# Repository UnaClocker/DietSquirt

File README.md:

# DietSquirt
Version 4.0 PCB Update October 2026
Migrated to KiCad 10.0, no more legacy Eagle requirements. The board is a 4 layer 100x100mm PCB now. Updated some components, 
switched to more common and standard sized components. As of the time of this writing, the boards are in production.
Included injector and coil drivers both this time. I know the injector drivers I picked will work with at least 2x 
high impedance injectors each.
I will update as needed with the results of the first test batch. Included the exact gerbers I submitted, but I have
made some minor changes to the silkscreen on the back of the PCB since then. One way or another, I'd like to have a 
functioning PCB to use in a vehicle in the next month, so this version will be fully tested here soon.
B&G actually sent me a cease and desist back when I first released this 10 years ago. Based on some obscure patent.
Well, it's been long enough that a patent would have expired by now. Given they started MegaSquirt around 2002, 
patents only last 17 years and it's going on 25 now... I kept the Anonymous name on there to keep up the rebel
spirit of this thing.
I still have a pile of MS1 CPU's, so this board is still 68hc908 centric. But a minor refactoring would make it 
perfectly happy with the MS2 CPU module or even MS3.

--- Old notes circa 2017 ---

Low cost DIY open source MegaSquirt derivative.

Welcome to my incomplete project. This was meant to be a much cheaper 
alternative to MegaSquirt. It uses the same processor as the MegaSquirt,
which is wired the same way as you might wire it for MegaSquirt-Extra 
firmware. Now being that this is not a licensed board, you shouldn’t run 
their firmware on it. But if you do, who am I to stop you. ;) You’re not 
supposed to run MegaSquirt on street cars either, but most MegaSquirt users 
do.

Please watch the video about this: https://www.youtube.com/watch?v=LJTZ3sH1d-M

This project is licensed under the BSD License. Take it and do anything with
it. If you mass produce and sell it, I hope you’re not using the MegaSquirt 
firmware, their lawyers will bury you. Your own personal use, totally another 
matter, not worth coming after Joe Blow who’s running it in their own car. 
Ideally, the MegaSquirt firmware can prove the board, then we can switch to 
a far better processor and far more open firmware like the STM32F4 with 
RusEFI firmware. I signed the board “Anonymous” because of the risk of 
B&G’s lawyers. 

As stated, this board is a work in progress. I’d like to say I can come 
back and finish it, but I designed it two years ago, maybe 2 1/2 years at 
this point. Right after that I discovered my wife was having an affair 
(TMI…), and entered a long drawn out divorce. Now I’m a single father of 
two kids so I don’t have much time to devote to these projects anymore. 
I’m placing the files on Github, we can work together to update and fix 
the board as testing progresses.
Current known issues: 
	The components for the voltage regulator circuit are too big and 
don’t fit. Namely the capacitors. 
	It needs the LC filter added between the output of the VR and the 
rest of the board to clean up the noise from the switch mode power supply. 
See the data sheet to the 34063 voltage regulator for that circuit.
	The DB15 and DB25 connectors are too far inboard, they need to be 
shifted out to the next mark on the silkscreen.

Next up, this board does not have onboard injector drivers. I had intended 
it to use the JBPerf P&H board. He seems to have stopped selling it since 
then, so I, or someone else may need to create a clone of his old board. 
It’s a very very simple circuit board to make. The chips are still available.

You can submit the .brd files to OSHPark.com to have 3 copies of the board 
made. It’s VERY expensive there. but if you’re in the US, they’re very fast. 
You can get 10 boards made at www.elecrow.com, under their 5cmx10cm pricing, 
I believe it’s $20 for 10 boards. Give the spare boards to friends, or save 
them as spares. Don’t sell them, you’ll risk the wrath of the B&G lawyers.

See the attached BOM for the list of parts you’ll want to order from Digikey 
for this board.

The files are for Eagle. Place the .brd and .sch files in a DietSquirt folder
under your main eagle projects, then load the .sch schematic file and .brd board 
layout file. The gerbers are included, but since the board needs work still, 
I wouldn't suggest building having it produced. At the very least, you'd have 
to run an external 5v voltage regulator. I'd have prefered to have done the 
board in KiCad, but I knew Eagle better at the time. You can get a free version 
of Eagle, google it, download it. Works in all 3 major OS's.

I’m probably forgetting a lot. I’ll document more as time allows. 
Questions? unaclocker@gmail.com

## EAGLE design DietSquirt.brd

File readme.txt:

Welcome to my incomplete project. This was meant to be a much cheaper 
alternative to MegaSquirt. It uses the same processor as the MegaSquirt,
which is wired the same way as you might wire it for MegaSquirt-Extra 
firmware. Now being that this is not a licensed board, you shouldn’t run 
their firmware on it. But if you do, who am I to stop you. ;) You’re not 
supposed to run MegaSquirt on street cars either, but most MegaSquirt users 
do.
Please watch the video about this which will be posted on YouTube shortly.
This project is licensed under the BSD License. Take it and do anything with
it. If you mass produce and sell it, I hope you’re not using the MegaSquirt 
firmware, their lawyers will bury you. Your own personal use, totally another 
matter, not worth coming after Joe Blow who’s running it in their own car. 
Ideally, the MegaSquirt firmware can prove the board, then we can switch to 
a far better processor and far more open firmware like the STM32F4 with 
RusEFI firmware. I signed the board “Anonymous” because of the risk of 
B&G’s lawyers. 
As stated, this board is a work in progress. I’d like to say I can come 
back and finish it, but I designed it two years ago, maybe 2 1/2 years at 
this point. Right after that I discovered my wife was having an affair 
(TMI…), and entered a long drawn out divorce. Now I’m a single father of 
two kids so I don’t have much time to devote to these projects anymore. 
I’m placing the files on Github, we can work together to update and fix 
the board as testing progresses.
Current known issues: 
	The components for the voltage regulator circuit are too big and 
don’t fit. Namely the capacitors. 
	It needs the LC filter added between the output of the VR and the 
rest of the board to clean up the noise from the switch mode power supply. 
See the data sheet to the 34063 voltage regulator for that circuit.
	The DB15 and DB25 connectors are too far inboard, they need to be 
shifted out to the next mark on the silkscreen.

Next up, this board does not have onboard injector drivers. I had intended 
it to use the JBPerf P&H board. He seems to have stopped selling it since 
then, so I, or someone else may need to create a clone of his old board. 
It’s a very very simple circuit board to make. The chips are still available.

You can submit the .brd files to OSHPark.com to have 3 copies of the board 
made. It’s VERY expensive there. but if you’re in the US, they’re very fast. 
You can get 10 boards made at www.elecrow.com, under their 5cmx10cm pricing, 
I believe it’s $20 for 10 boards. Give the spare boards to friends, or save 
them as spares. Don’t sell them, you’ll risk the wrath of the B&G lawyers.

See the attached BOM for the list of parts you’ll want to order from Digikey 
for this board.

The files are for Eagle. Load the .pro project file, then load the .sch 
schematic file and .brd board layout file. The gerbers are included, but 
since the board needs work still, I wouldn't suggest building it. At the 
very least, you'd have to run an external 5v voltage regulator. I'd have 
prefered to have done the board in KiCad,
but I knew Eagle better at the time. You can get a free version of Eagle, 
google it, download it. Works in all 3 major OS's.

I’m probably forgetting a lot. I’ll document more as time allows. 
Questions? unaclocker@gmail.com

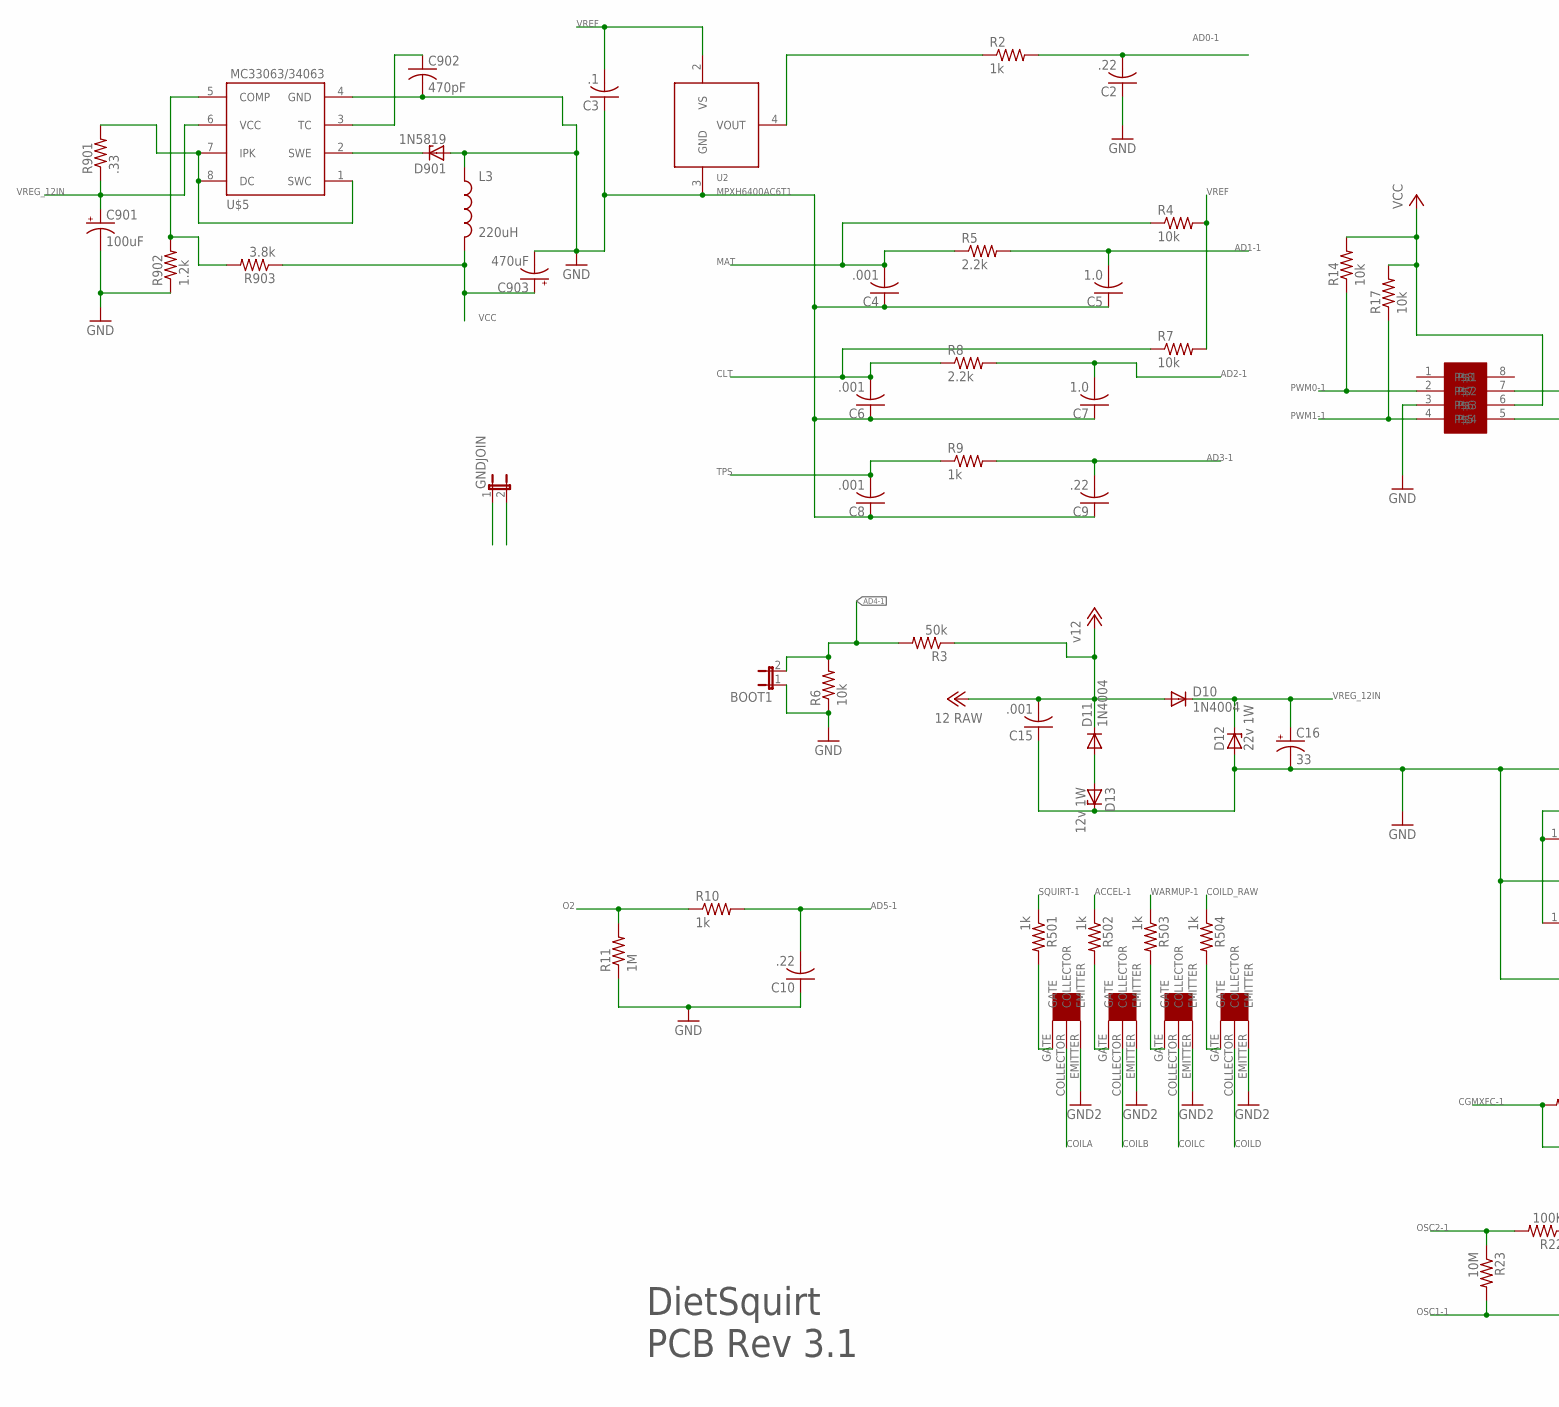
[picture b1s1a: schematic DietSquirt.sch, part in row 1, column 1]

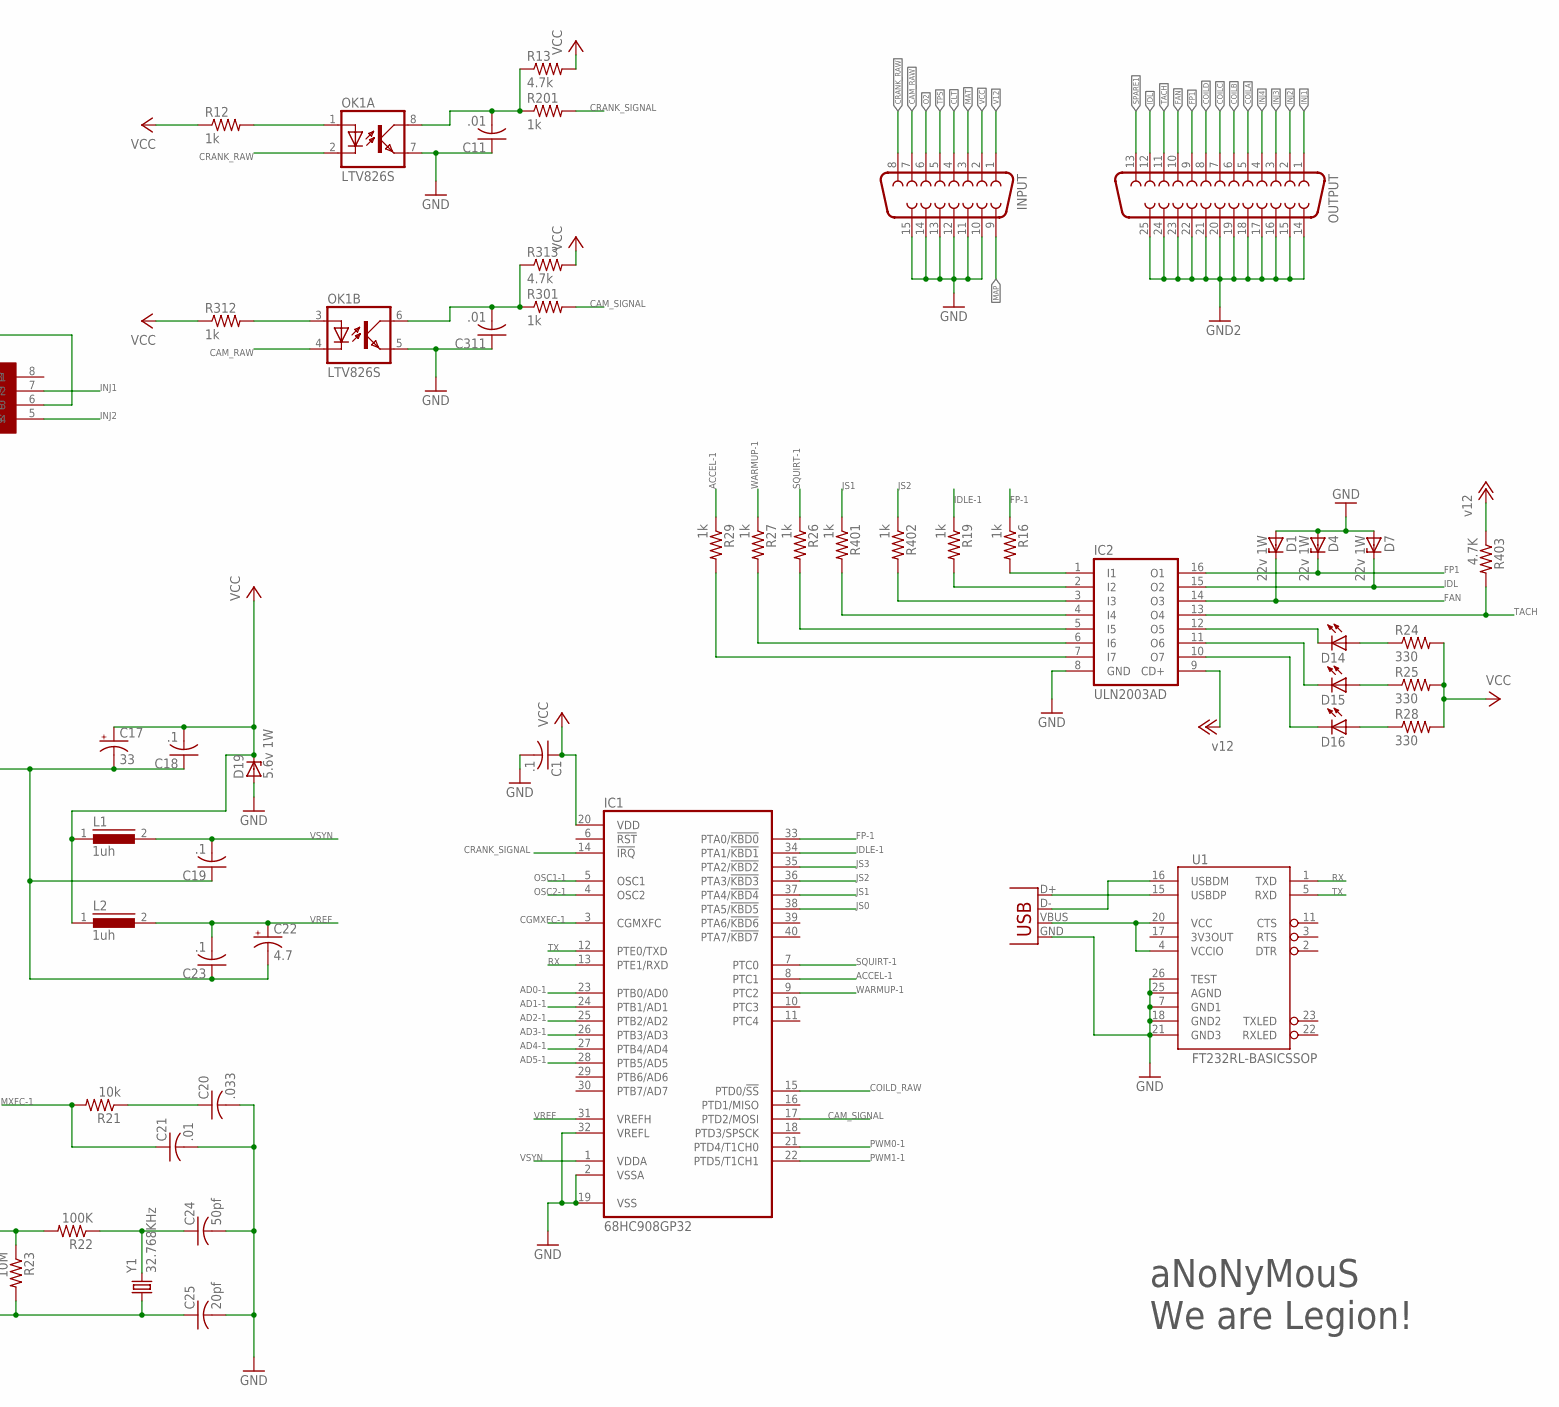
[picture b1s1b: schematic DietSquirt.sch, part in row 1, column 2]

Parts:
BOOT1: JUMPER-2PTH; 1X02
C1, C3, C18, C19, C23: .1; C0805
C2, C9, C10: .22; C0805
C4, C6, C8, C15: .001; C0805
C5, C7: 1.0; C0805
C11, C21, C311: .01; C0805
C16, C17: 33; C/6032-28R
C20: .033; C0805
C22: 4.7; C/6032-28R
C24: 50pf; C0805
C25: 20pf; C0805
C901: 100uF; C/6032-28R
C902: 470pF; C0805
C903: 470uF; C/6032-28R
COILA: ISL9V3036S3ST; TO263
COILB: ISL9V3036S3ST; TO263
COILC: ISL9V3036S3ST; TO263
COILD: ISL9V3036S3ST; TO263
D1, D4, D7, D12: 22v 1W; DO41Z10
D10, D11: 1N4004; DO41-10
D13: 12v 1W; DO41Z10
D14, D15, D16: LEDCHIPLED_0805; CHIPLED_0805
D19: 5.6v 1W; DO41Z10
D901: 1N5819; DO41Z10
GNDJOIN: JUMPER-2PTH; 1X02
IC1: 68HC908GP32; DIL40
IC2: ULN2003AD; SO16
INPUT: F15H
L1, L2: 1uh; MICC12
L3: 220uH; NPI75C
OK1: LTV826S; DIL8-SMD
OUTPUT: F25H
R2, R9, R10, R12, R16, R19, R26, R27, R29, R201, R301, R312, R401, R402, R501, R502, R503, R504: 1k; R0805
R3: 50k; R0805
R4, R6, R7, R14, R17, R21: 10k; R0805
R5, R8: 2.2k; R0805
R11: 1M; R0805
R13, R313: 4.7k; R0805
R22: 100K; R0805
R23: 10M; R0805
R24, R25, R28: 330; R0805
R403: 4.7K; R0805
R901: .33; R0805
R902: 1.2k; R0805
R903: 3.8k; R0805
U1: FT232RL-BASICSSOP; SSOP28DB
U2: MPXH6400AC6T1; SSOP8
U$1: MC34151; SO08
U$5: MC33063/MC34063D; SO08
X1: USB-MICROB
Y1: 32.768KHz; TC26H

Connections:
+12V: IC2.9 (CD+), R403.1
ACCEL-1: IC1.8 (PTC1), R29.1, R502.1
AD0-1: C2.2, IC1.23 (PTB0/AD0), R2.2
AD1-1: C5.2, IC1.24 (PTB1/AD1), R5.2
AD2-1: C7.2, IC1.25 (PTB2/AD2), R8.2
AD3-1: C9.2, IC1.26 (PTB3/AD3), R9.2
AD4-1: BOOT1.2, IC1.27 (PTB4/AD4), R3.2, R6.2
AD5-1: C10.2, IC1.28 (PTB5/AD5), R10.2
CAM_RAW: INPUT.7, OK1.4 (C)
CAM_SIGNAL: IC1.17 (PTD2/MOSI), R301.2
CGMXFC-1: C21.1, IC1.3 (CGMXFC), R21.2
CLT: C6.2, INPUT.4, R7.1, R8.1
COILA: COILA.COLLECTOR, OUTPUT.5
COILB: COILB.COLLECTOR, OUTPUT.6
COILC: COILC.COLLECTOR, OUTPUT.7
COILD: COILD.COLLECTOR, OUTPUT.8
COILD_RAW: IC1.15 (PTD0/!SS), R504.1
CRANK_RAW: INPUT.8, OK1.2 (C)
CRANK_SIGNAL: IC1.14 (!IRQ), R201.2
FAN: D1.C, IC2.14 (O3), OUTPUT.10
FP1: D4.C, IC2.16 (O1), OUTPUT.9
FP-1: IC1.33 (PTA0/!KBD0), R16.1
GND: BOOT1.1, C1.2, C2.1, C3.1, C4.1, C5.1, C6.1, C7.1, C8.1, C9.1, C10.1, C11.1, C15.1, C16.-, C17.-, C18.1, C19.1, C20.2, C21.2, C22.-, C23.1, C24.2, C25.2, C311.1, C901.-, C902.2, C903.-, D1.A, D4.A, D7.A, D12.A, D13.C, D19.A, D901.A, GNDJOIN.1, IC1.2 (VSSA), IC1.19 (VSS), IC1.32 (VREFL), IC2.8 (GND), INPUT.10, INPUT.11, INPUT.12, INPUT.13, INPUT.14, INPUT.15, L3.1, OK1.5 (EMIT), OK1.7 (EMIT), R6.1, R11.1, R902.1, U1.7 (GND1), U1.18 (GND2), U1.21 (GND3), U1.25 (AGND), U1.26 (TEST), U2.3 (GND), U$1.3, U$5.4 (GND), X1.GND
GND2: COILA.EMITTER, COILB.EMITTER, COILC.EMITTER, COILD.EMITTER, GNDJOIN.2, OUTPUT.14, OUTPUT.15, OUTPUT.16, OUTPUT.17, OUTPUT.18, OUTPUT.19, OUTPUT.20, OUTPUT.21, OUTPUT.22, OUTPUT.23, OUTPUT.24, OUTPUT.25
IDL: D7.C, IC2.15 (O2), OUTPUT.12
IDLE-1: IC1.34 (PTA1/!KBD1), R19.1
INJ1: OUTPUT.1, U$1.7
INJ2: OUTPUT.2, U$1.5
INJ3: OUTPUT.3
INJ4: OUTPUT.4
JS0: IC1.38 (PTA5/!KBD5)
JS1: IC1.37 (PTA4/!KBD4), R401.1
JS2: IC1.36 (PTA3/!KBD3), R402.1
JS3: IC1.35 (PTA2/!KBD2)
MAP: INPUT.9, R2.1, U2.4 (VOUT)
MAT: C4.2, INPUT.3, R4.1, R5.1
unnamed: C24.1, R22.1, Y1.2
unnamed: OK1.1 (A), R12.2
unnamed: C20.1, R21.1
unnamed: OK1.3 (A), R312.2
unnamed: D11.A, D13.A
unnamed: IC2.1 (I1), R16.2
unnamed: IC2.2 (I2), R19.2
unnamed: C11.2, OK1.8 (COL), R13.1, R201.1
unnamed: C311.2, OK1.6 (COL), R301.1, R313.1
unnamed: U1.4 (VCCIO), U1.20 (VCC), X1.VBUS
unnamed: D901.C, U$5.2 (SWE)
unnamed: IC2.3 (I3), R402.2
unnamed: U1.16 (USBDM), X1.D-
unnamed: U1.15 (USBDP), X1.D+
unnamed: IC2.4 (I4), R401.2
unnamed: IC2.5 (I5), R26.2
unnamed: IC2.6 (I6), R27.2
unnamed: IC2.7 (I7), R29.2
unnamed: D14.C, IC2.12 (O5)
unnamed: D15.C, IC2.11 (O6)
unnamed: D16.C, IC2.10 (O7)
unnamed: D16.A, R28.1
unnamed: D15.A, R25.1
unnamed: D14.A, R24.1
unnamed: COILA.GATE, R501.2
unnamed: COILB.GATE, R502.2
unnamed: COILC.GATE, R503.2
unnamed: R901.2, U$5.1 (SWC), U$5.7 (IPK), U$5.8 (DC)
unnamed: R902.2, R903.2, U$5.5 (COMP)
unnamed: COILD.GATE, R504.2
unnamed: C902.1, U$5.3 (TC)
O2: INPUT.6, R10.1, R11.2
OSC1-1: C25.1, IC1.5 (OSC1), R23.2, Y1.1
OSC2-1: IC1.4 (OSC2), R22.2, R23.1
PWM0-1: IC1.21 (PTD4/T1CH0), R14.1, U$1.2
PWM1-1: IC1.22 (PTD5/T1CH1), R17.1, U$1.4
RX: IC1.13 (PTE1/RXD), U1.1 (TXD)
SPARE1: OUTPUT.13
SQUIRT-1: IC1.7 (PTC0), R26.1, R501.1
TACH: IC2.13 (O4), OUTPUT.11, R403.2
TPS: C8.2, INPUT.5, R9.1
TX: IC1.12 (PTE0/TXD), U1.5 (RXD)
V12: C15.2, D10.A, D11.C, INPUT.1, R3.1
VCC: C1.1, C17.+, C18.2, C903.+, D19.C, IC1.20 (VDD), INPUT.2, L1.1, L2.1, L3.2, R12.1, R13.2, R14.2, R17.2, R24.2, R25.2, R28.2, R312.1, R313.2, R903.1, U$1.6
VREF: C3.2, C22.+, C23.2, IC1.31 (VREFH), L2.2, R4.2, R7.2, U2.2 (VS)
VREG_12IN: C16.+, C901.+, D10.C, D12.C, R901.1, U$5.6 (VCC)
VSYN: C19.2, IC1.1 (VDDA), L1.2
WARMUP-1: IC1.9 (PTC2), R27.1, R503.1

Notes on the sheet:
DietSquirt PCB Rev 3.1
aNoNyMouS We are Legion!

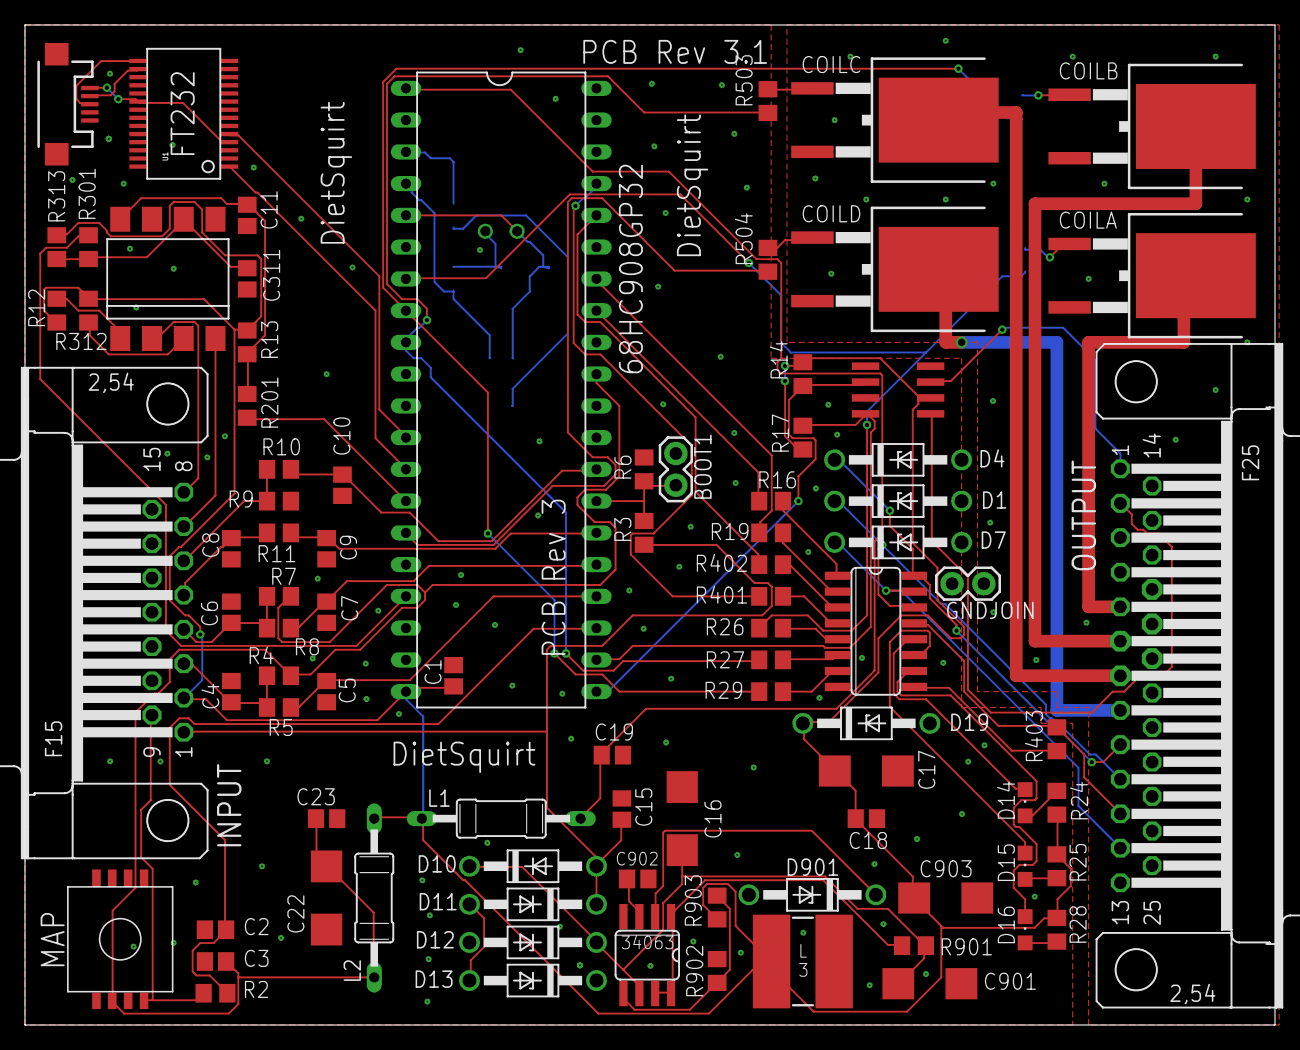
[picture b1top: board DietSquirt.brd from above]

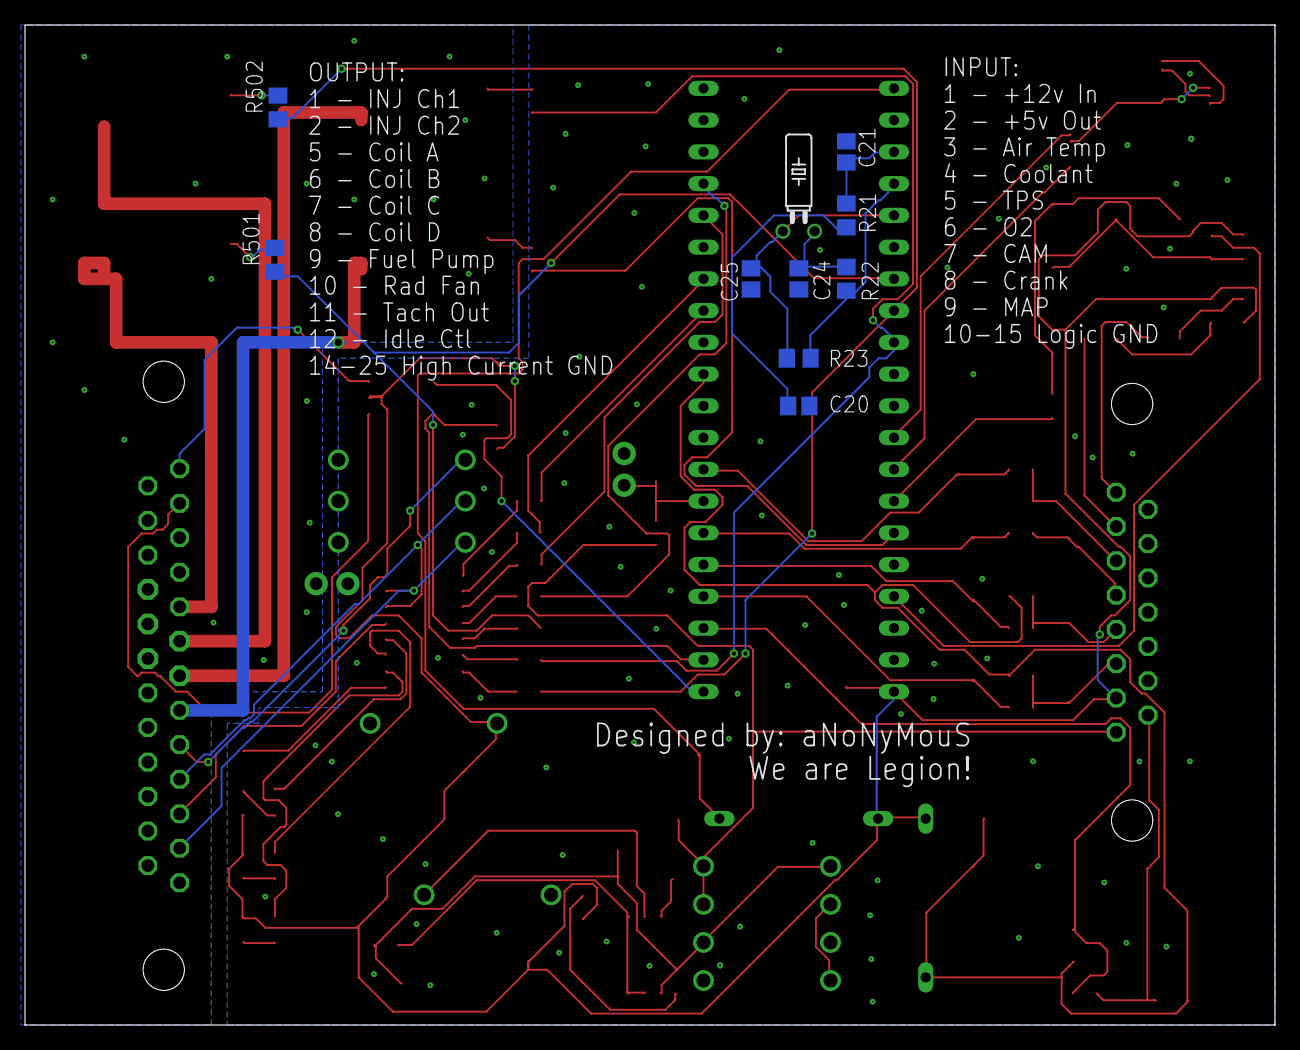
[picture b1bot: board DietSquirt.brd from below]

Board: 2 copper layers, 100.0 x 80.0 mm, 97 parts (10 on the bottom side), 79 nets.

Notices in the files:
parts and their libraries:
SparkFun: Licensing: CC v3.0 Share-Alike You are welcome to use this library for commercial purposes.
